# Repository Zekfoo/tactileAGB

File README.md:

# Background

CURRENT VERSION - REV 1.1

This mod for the Game Boy Advance (AGB) was inspired by makho's [AGB_TACT](https://github.com/makhowastaken/AGB_TACT) project which added tactile buttons to the AGB to create a similar clicky feel to the GBA SP and more recent Nintendo handhelds.

Developed from the ground up, this implementation offers a no-wires-required solution, consisting of 3 flex breakout boards for the DPAD, A/B, and START/SELECT.

# Mod Compatibility

This mod is only compatible with AGB-001. 

Due to variability between OEM and different aftermarket buttons and membranes, some adjustments may need to be made to adjust the button height and travel distances - more details in the Installation section.

Compatibility with the IPS v2 mod's brightness controls is ensured - just solder the SELECT wire overtop of the TP2 hole.

# Board and Parts Links

Flex board order link ($20.70 for 3 sets) - [OSH Park](https://oshpark.com/shared_projects/KdYTs0bl)

SKRRABE010 (for DPAD and A/B - GBA SP Buttons) - [Mouser](https://www.mouser.com/ProductDetail/?qs=m0BA540hBPcAX44PgGtO0w%3D%3D)

SOG-152ANT (for START/SELECT) - [Digikey](https://www.digikey.ca/en/products/detail/mitsumi-electric-company-ltd/SOG-152ANT/11591283)

# Disclaimer

As with all hardware mods, you risk irreparable damage to your device if the proper precautions are not taken. Feel free to reach out for any questions or troubleshooting.

# Installation

**General:**
* Solder SKRRABE010 buttons to their corresponding footprints on the DPAD and A/B flex boards
* Solder SOG-152ANT buttons to their corresponding footprints on the START/SELECT flex board

**DPAD**
* Line up the holes labelled TP4, TP5, and TP7 with the corresponding testpoints on the AGB board, this should align all solder points with their corresponding contacts
* Solder:
  * TP4, TP5, TP6, and TP7 for each of the 4 DPAD buttons
  * Ground connection to the pad of the L button shielding
  * (Optional) VDD-15 can be used as an anchor point

**A/B**
* Line up the holes labelled TP0 and TP1 with the corresponding test points on the AGB board
* Solder:
  * TP0 and TP1 for A and B respectively
  * Ground connection to upper right GND pad
  * (Optional) FR2 can be used as an anchor point

**START/SELECT**
* Line up the holes labelled TP2 and TP3 with the corresponding test points on the AGB board
* Solder:
  * TP2 and TP3 for SELECT and START respectively
  * Ground connection to left GND pad
  * (For IPS v2 brightness controls) Solder the SELECT wire from the IPS ribbon cable overtop of the TP2 hole.

**Button height/travel**
* The button travel distance may need to be adjusted based on individual preference - simply insert some thin cardboard between the tactile buttons and membranes in order to shorten the travel distance 
* Cardboard may also need to be inserted under the center of the DPAD membrane in order to raise its pivot point - a properly functioning DPAD should only be able to register 2 directions at the same time - if you own a flash cart, you can check using this [ROM](https://github.com/heroldev/AGB-buttontest)

# Acknowledgements

Thanks to [makho](https://www.youtube.com/channel/UC5FYpo9lFqK1Y7wqjPuANFw) for his original project idea and video.

Thanks to [HDR](https://martinrefseth.com/) for compiling his Nintenfo repository, which made development much swifter.

# License

<br />This work is licensed under a <a rel="license" href="http://creativecommons.org/licenses/by-nc-sa/4.0/">Creative Commons Attribution-NonCommercial-ShareAlike 4.0 International License</a>.

Feel free to modify this design however you like, but please make sure to give credit where it is due. I encourage you to share your improvements with the rest of the Gameboy modding community at the Gameboy [Discord](https://discord.gg/RYN3bMxr) and [Subreddit](https://www.reddit.com/r/Gameboy/)

Under this license, you are not permitted to profit from or commercialize this design in any part without my express permission.

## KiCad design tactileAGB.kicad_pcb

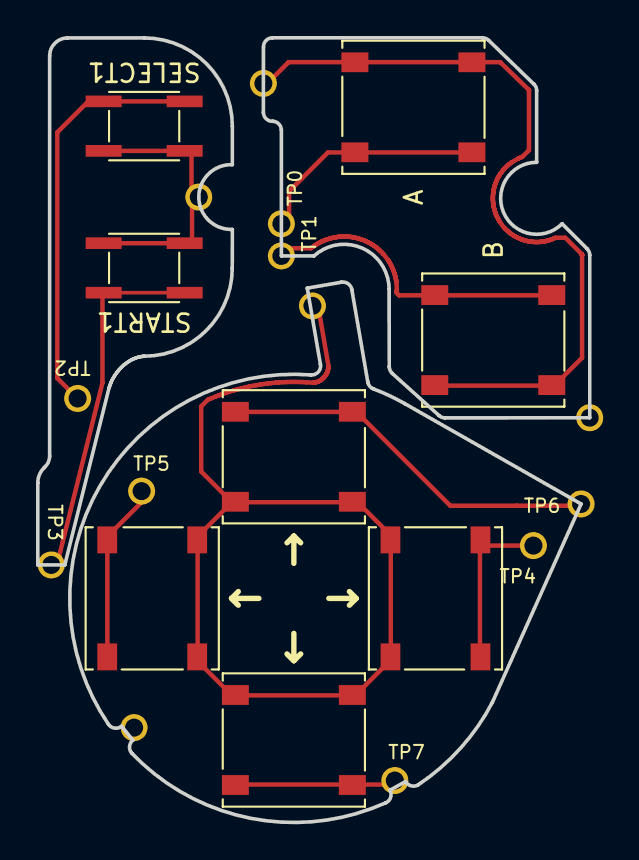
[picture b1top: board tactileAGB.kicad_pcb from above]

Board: 2 copper layers, 30.7 x 43.6 mm, 21 parts (0 on the bottom side), 11 nets.

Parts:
A: SKRRABE010
B: SKRRABE010
FR2: TestPoint; Hole-1.5mm
GND2PAD1, GND3PAD1: TestPoint; Hole-1.5mm
L-SHIELDING1: TestPoint; Hole-1.5mm
SELECT1: SOG-152ANT; SOG-15xANT
START1: SOG-152ANT; SOG-15xANT
TP0, TP1, TP2, TP3, TP4, TP5, TP6, TP7: TestPoint; Hole-1.5mm
VDD-15: TestPoint; Hole-1.5mm
↑: SKRRABE010
↑#2, ↑#3, ↑#4: SKRRABE010

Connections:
GND1: L-SHIELDING1.1, ↑.3, ↑.4, ↑#2.3, ↑#2.4, ↑#3.3, ↑#3.4, ↑#4.3, ↑#4.4
GND2: GND2PAD1.1, SELECT1.3, SELECT1.4, START1.3, START1.4
GND3: A.3, A.4, B.3, B.4, GND3PAD1.1
unnamed: A.1, A.2, TP0.1
unnamed: B.1, B.2, TP1.1
unnamed: TP7.1, ↑.1, ↑.2
unnamed: TP5.1, ↑#2.1, ↑#2.2
unnamed: TP4.1, ↑#3.1, ↑#3.2
unnamed: SELECT1.1, SELECT1.2, TP2.1
unnamed: START1.1, START1.2, TP3.1
unnamed: TP6.1, ↑#4.1, ↑#4.2

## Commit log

2021-06-21 Initial commit - rev 1.0
2021-06-21 Fixed naming of testpoint VDD-15
2021-06-21 Reduced gerber size to lower OSH Park cost
2021-07-08 Rev 1.1 - changed to GBA SP buttons, removed NoStartSelect gerber option
2021-07-08 Updated PCB preview for rev 1.1
